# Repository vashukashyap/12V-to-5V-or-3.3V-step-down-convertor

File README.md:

# Step Down Convertor
A step down convertor which convert 12v to 5V and 3.3V output.
## Schematic

## PCB Board

## 3D Model

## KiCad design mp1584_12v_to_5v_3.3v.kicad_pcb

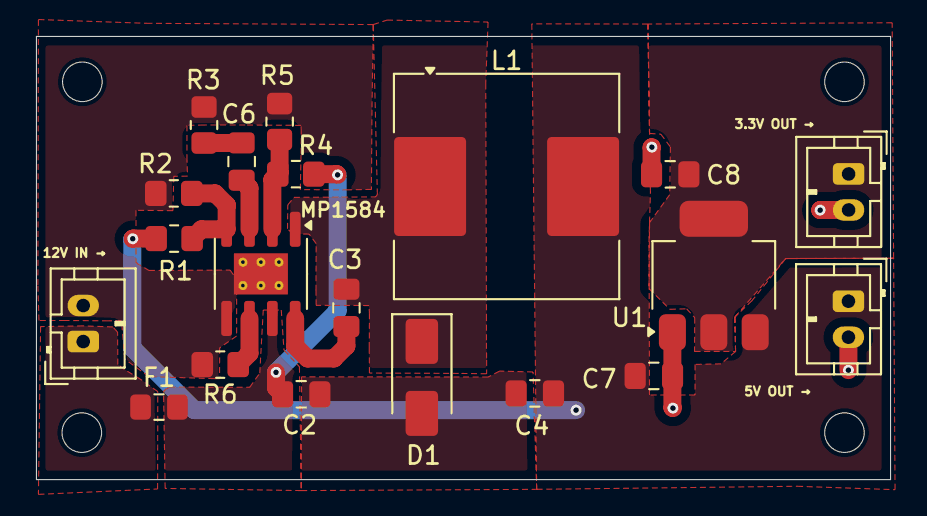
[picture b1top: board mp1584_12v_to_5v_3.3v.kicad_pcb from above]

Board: 2 copper layers, 47.4 x 24.6 mm, 24 parts (0 on the bottom side), 12 nets.

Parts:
3.3V OUT →, 5V OUT →, 12V IN →: Conn_01x02_Socket; JST_PH_B2B-PH-K_1x02_P2.00mm_Vertical
C2, C7, C8: 10uf; C_0805_2012Metric_Pad1.18x1.45mm_HandSolder
C3: 100nf; C_0805_2012Metric_Pad1.18x1.45mm_HandSolder
C4: 22uf; C_0805_2012Metric_Pad1.18x1.45mm_HandSolder
C6: 150pf; C_0805_2012Metric_Pad1.18x1.45mm_HandSolder
D1: D_Schottky; D_SMA
F1: Polyfuse; Fuse_0805_2012Metric_Pad1.15x1.40mm_HandSolder
H1, H2, H3, H4: MountingHole; MountingHole_2.2mm_M2
L1: 15uH; L_Coilcraft_MSS1278-XXX
MP1584: U; SOIC-8-1EP_3.9x4.9mm_P1.27mm_EP2.29x3mm_ThermalVias
R1: 210kohm; R_0805_2012Metric_Pad1.20x1.40mm_HandSolder
R2: 40.2kohm; R_0805_2012Metric_Pad1.20x1.40mm_HandSolder
R3, R4, R6: 100kohm; R_0805_2012Metric_Pad1.20x1.40mm_HandSolder
R5: 24.9kohm; R_0805_2012Metric_Pad1.20x1.40mm_HandSolder
U1: AMS1117-3.3; SOT-223-3_TabPin2

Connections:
12V_Input: 12V IN →.1, F1.1
GND: 3.3V OUT →.2, 5V OUT →.2, 12V IN →.2, C2.2, C4.2, C7.2, C8.2, D1.2 (A), MP1584.5 (GND), MP1584.9 (EPAD), R2.1, R3.1, R5.1, R6.2, U1.1 (GND)
unnamed: C6.1, R3.2
unnamed: C3.2, MP1584.8 (BST)
unnamed: C6.2, MP1584.3 (COMP)
unnamed: MP1584.2 (EN), R4.2, R5.2
unnamed: MP1584.4 (FB), R1.2, R2.2
unnamed: MP1584.6 (FREQ), R6.1
SW_OUT: C3.1, D1.1 (K), L1.1, MP1584.1 (SW)
VIN: C2.1, F1.2, MP1584.7 (VIN), R4.1
VOUT_3.3V: 3.3V OUT →.1, C8.1, U1.2 (VO)
VOUT_5V: 5V OUT →.1, C4.1, C7.1, L1.2, R1.1, U1.3 (VI)

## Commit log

2026-03-20 task completed
2026-03-20 Add README for step down convertor project
    Added basic information about the step down convertor, including schematic and PCB board images.
2026-03-20 Add 3D Model section to README
    Added section for 3D Model with images.
